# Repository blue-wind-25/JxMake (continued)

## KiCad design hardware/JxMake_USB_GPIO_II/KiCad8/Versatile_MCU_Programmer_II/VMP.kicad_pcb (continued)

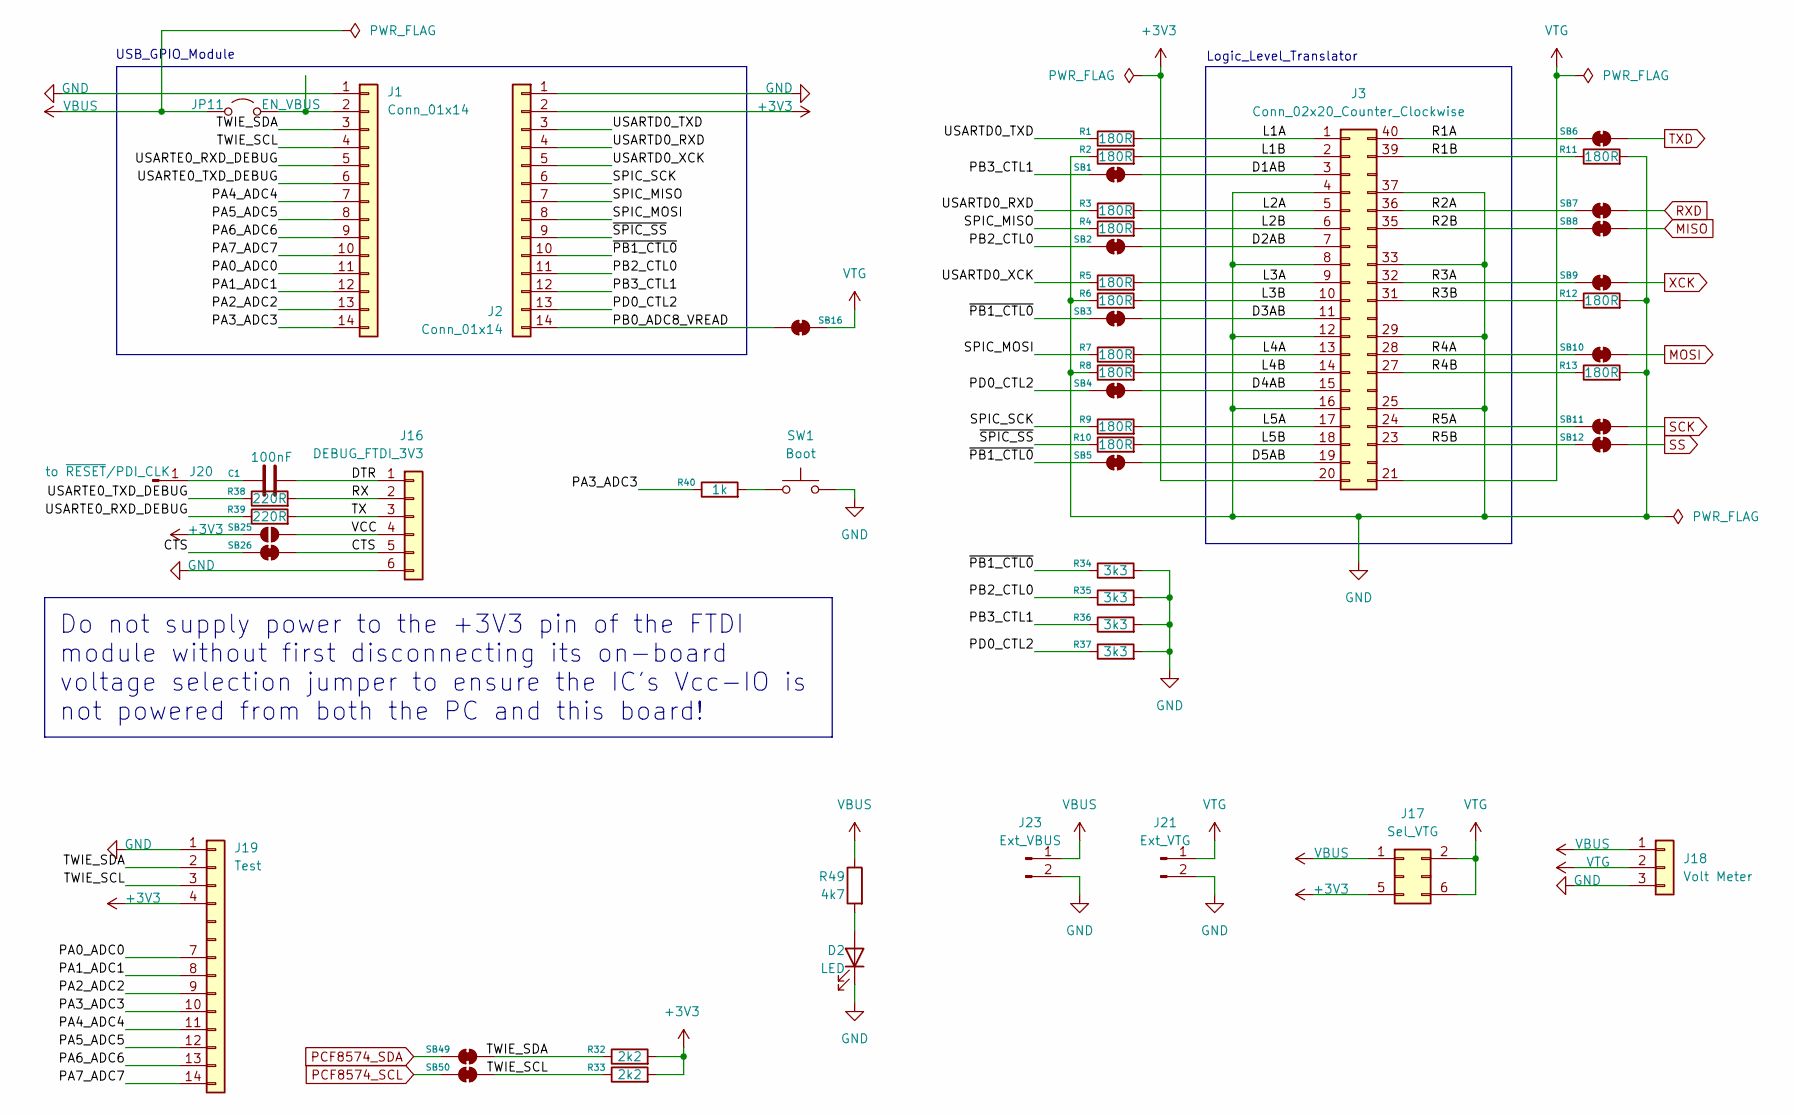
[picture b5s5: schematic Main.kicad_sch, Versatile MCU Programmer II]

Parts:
C1: 100nF; C_0805_2012Metric_Pad1.18x1.45mm_HandSolder
D2: LED; LED_0805_2012Metric_Pad1.15x1.40mm_HandSolder
J1, J2: Conn_01x14; PinHeader_1x14_P2.54mm_Vertical
J3: Conn_02x20_Counter_Clockwise; DIP-40_W25.4mm_LongPads
J16: DEBUG_FTDI_3V3; PinSocket_1x06_P2.54mm_Horizontal
J17: Sel_VTG; PinHeader_2x03_P2.54mm_Vertical
J18: Volt Meter; Molex_KK-254_AE-6410-03A_1x03_P2.54mm_Vertical
J19: Test; PinHeader_1x14_P2.54mm_Vertical
J20: to ~{RESET}/PDI_CLK; PinHeader_1x01_P2.54mm_Vertical
J21: Ext_VTG; Molex_KK-254_AE-6410-02A_1x02_P2.54mm_Vertical
J23: Ext_VBUS; Molex_KK-254_AE-6410-02A_1x02_P2.54mm_Vertical
JP11: EN_VBUS; PinHeader_1x02_P2.54mm_Vertical
R1, R2, R3, R4, R5, R6, R7, R8, R9, R10, R11, R12, R13: 180R; R_0805_2012Metric_Pad1.20x1.40mm_HandSolder
R32, R33: 2k2; R_0805_2012Metric_Pad1.20x1.40mm_HandSolder
R34, R35, R36, R37: 3k3; R_0805_2012Metric_Pad1.20x1.40mm_HandSolder
R38, R39: 220R; R_0805_2012Metric_Pad1.20x1.40mm_HandSolder
R40: 1k; R_0805_2012Metric_Pad1.20x1.40mm_HandSolder
R49: 4k7; R_0805_2012Metric_Pad1.20x1.40mm_HandSolder
SB1, SB2, SB3, SB4, SB5, SB6, SB7, SB8, SB9, SB10, SB11, SB12, SB16, SB26, SB49, SB50: Jumper_2_Small_Bridged; SolderJumper-2_P1.3mm_Bridged_Pad1.0x1.5mm
SB25: Jumper_2_Small_Open; SolderJumper-2_P1.3mm_Open_Pad1.0x1.5mm
SW1: Boot; SW_SPST_FSMSM

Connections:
+3V3: J2.2, J3.20, J17.5, J19.4, R32.2, R33.2, SB25.1 (A); also elsewhere on the board
/Main/CTS: J16.5, SB26.1 (A), SB26.2 (B)
/Main/D1AB: J3.3, SB1.2 (B)
/Main/D2AB: J3.7, SB2.2 (B)
/Main/D3AB: J3.11, SB3.2 (B)
/Main/D4AB: J3.15, SB4.2 (B)
/Main/D5AB: J3.19, SB5.2 (B)
/Main/DTR: C1.2, J16.1
/Main/L1A: J3.1, R1.2
/Main/L1B: J3.2, R2.2
/Main/L2A: J3.5, R3.2
/Main/L2B: J3.6, R4.2
/Main/L3A: J3.9, R5.2
/Main/L3B: J3.10, R6.2
/Main/L4A: J3.13, R7.2
/Main/L4B: J3.14, R8.2
/Main/L5A: J3.17, R9.2
/Main/L5B: J3.18, R10.2
/Main/PA0_ADC0: J1.11, J19.7
/Main/PA1_ADC1: J1.12, J19.8
/Main/PA2_ADC2: J1.13, J19.9
/Main/PA3_ADC3: J1.14, J19.10, R40.1
/Main/PA4_ADC4: J1.7, J19.11
/Main/PA5_ADC5: J1.8, J19.12
/Main/PA6_ADC6: J1.9, J19.13
/Main/PA7_ADC7: J1.10, J19.14
/Main/PB0_ADC8_VREAD: J2.14, SB16.2 (B)
/Main/PB2_CTL0: J2.11, R35.1, SB2.1 (A)
/Main/PB3_CTL1: J2.12, R36.1, SB1.1 (A)
/Main/PD0_CTL2: J2.13, R37.1, SB4.1 (A)
/Main/R1A: J3.40, SB6.1 (A)
/Main/R1B: J3.39, R11.1
/Main/R2A: J3.36, SB7.1 (A)
/Main/R2B: J3.35, SB8.1 (A)
/Main/R3A: J3.32, SB9.1 (A)
/Main/R3B: J3.31, R12.1
/Main/R4A: J3.28, SB10.1 (A)
/Main/R4B: J3.27, R13.1
/Main/R5A: J3.24, SB11.1 (A)
/Main/R5B: J3.23, SB12.1 (A)
/Main/RX: J16.2, R38.2
/Main/SPIC_MISO: J2.7, R4.1
/Main/SPIC_MOSI: J2.8, R7.1
/Main/SPIC_SCK: J2.6, R9.1
/Main/TWIE_SCL: J1.4, J19.3, R33.1, SB50.2 (B)
/Main/TWIE_SDA: J1.3, J19.2, R32.1, SB49.2 (B)
/Main/TX: J16.3, R39.2
/Main/USARTD0_RXD: J2.4, R3.1
/Main/USARTD0_TXD: J2.3, R1.1
/Main/USARTD0_XCK: J2.5, R5.1
/Main/USARTE0_RXD_DEBUG: J1.5, R39.1
/Main/USARTE0_TXD_DEBUG: J1.6, R38.1
/Main/VCC: J16.4, SB25.2 (B)
/Main/~PB1_CTL0: J2.10, R34.1, SB3.1 (A), SB5.1 (A)
/Main/~SPIC_SS: J2.9, R10.1
GND: D2.1 (K), J1.1, J2.1, J3.4, J3.8, J3.12, J3.16, J3.25, J3.29, J3.33, J3.37, J16.6, J18.3, J19.1, J21.2, J23.2, R2.1, R6.1, R8.1, R11.2, R12.2, R13.2, R34.2, R35.2, R36.2, R37.2, SW1.2; also elsewhere on the board
MISO: SB8.2 (B); also elsewhere on the board
MOSI: SB10.2 (B); also elsewhere on the board
unnamed: D2.2 (A), R49.2
unnamed: J1.2, JP11.2 (B)
unnamed: C1.1, J20.1
unnamed: R40.2, SW1.1
PCF8574_SCL: SB50.1 (A); also elsewhere on the board
PCF8574_SDA: SB49.1 (A); also elsewhere on the board
RXD: SB7.2 (B); also elsewhere on the board
SCK: SB11.2 (B); also elsewhere on the board
SS: SB12.2 (B); also elsewhere on the board
TXD: SB6.2 (B); also elsewhere on the board
VBUS: J17.1, J18.1, J23.1, JP11.1 (A), R49.1; also elsewhere on the board
VTG: J3.21, J17.2, J17.6, J18.2, J21.1, SB16.1 (A); also elsewhere on the board
XCK: SB9.2 (B); also elsewhere on the board

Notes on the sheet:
Do not supply power to the +3V3 pin of the FTDI module without first disconnecting its on-board voltage selection jumper to ensure the IC's Vcc-IO is not powered from both the PC and this board!
Logic_Level_Translator
USB_GPIO_Module

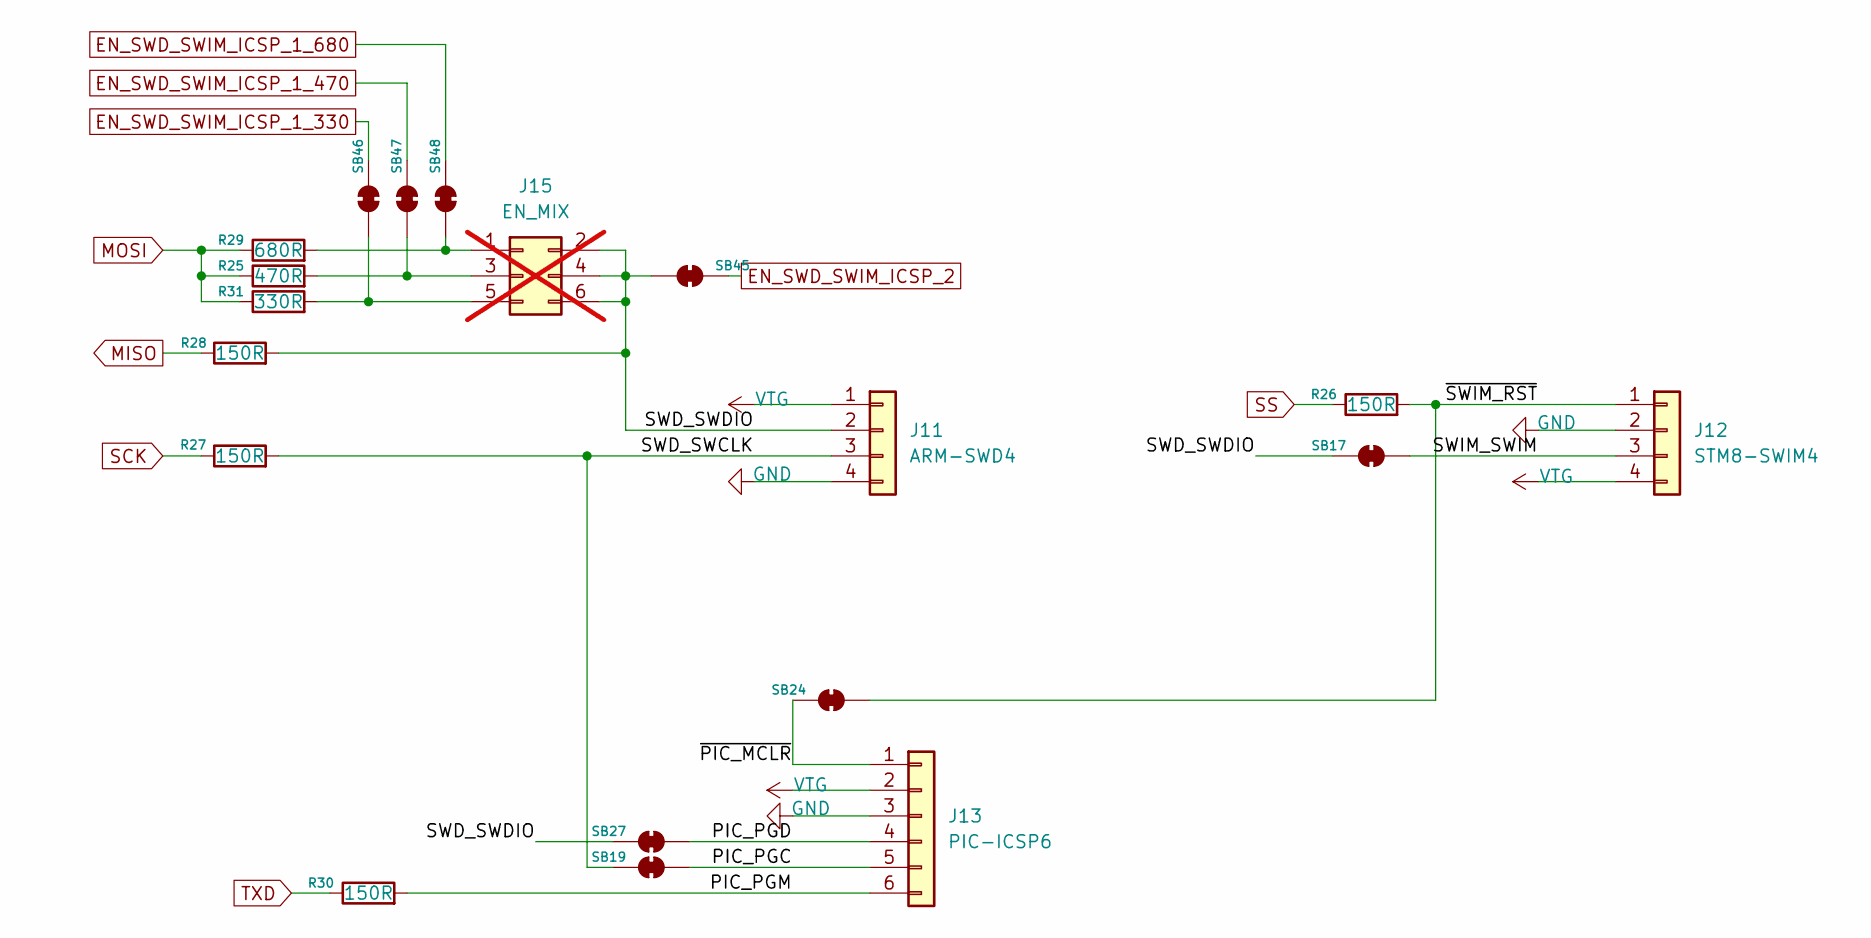
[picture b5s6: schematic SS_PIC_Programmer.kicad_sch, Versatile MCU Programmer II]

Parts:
J11: ARM-SWD4; PinSocket_1x04_P2.54mm_Horizontal
J12: STM8-SWIM4; PinSocket_1x04_P2.54mm_Horizontal
J13: PIC-ICSP6; PinSocket_1x06_P2.54mm_Horizontal
J15: EN_MIX; PinHeader_2x03_P2.54mm_Vertical; not fitted
R25: 470R; R_0805_2012Metric_Pad1.20x1.40mm_HandSolder
R26, R27, R28, R30: 150R; R_1206_3216Metric_Pad1.30x1.75mm_HandSolder
R29: 680R; R_0805_2012Metric_Pad1.20x1.40mm_HandSolder
R31: 330R; R_1206_3216Metric_Pad1.30x1.75mm_HandSolder
SB17, SB19, SB24, SB27, SB45, SB46, SB47, SB48: Jumper_2_Small_Bridged; SolderJumper-2_P1.3mm_Bridged_Pad1.0x1.5mm

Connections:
/SWD_SWIM_PIC_Programmer/PIC_PGC: J13.5, SB19.2 (B)
/SWD_SWIM_PIC_Programmer/PIC_PGD: J13.4, SB27.2 (B)
/SWD_SWIM_PIC_Programmer/PIC_PGM: J13.6, R30.2
/SWD_SWIM_PIC_Programmer/SWD_SWCLK: J11.3, R27.2, SB19.1 (A)
/SWD_SWIM_PIC_Programmer/SWD_SWDIO: J11.2, J15.2, J15.4, J15.6, R28.2, SB17.1 (A), SB27.1 (A), SB45.2 (B)
/SWD_SWIM_PIC_Programmer/SWIM_SWIM: J12.3, SB17.2 (B)
/SWD_SWIM_PIC_Programmer/~PIC_MCLR: J13.1, SB24.1 (A)
/SWD_SWIM_PIC_Programmer/~SWIM_RST: J12.1, R26.2, SB24.2 (B)
EN_SWD_SWIM_ICSP_1_330: SB46.1 (A); also elsewhere on the board
EN_SWD_SWIM_ICSP_1_470: SB47.1 (A); also elsewhere on the board
EN_SWD_SWIM_ICSP_1_680: SB48.1 (A); also elsewhere on the board
EN_SWD_SWIM_ICSP_2: SB45.1 (A); also elsewhere on the board
GND: J11.4, J12.2, J13.3; also elsewhere on the board
MISO: R28.1; also elsewhere on the board
MOSI: R25.1, R29.1, R31.1; also elsewhere on the board
unnamed: J15.1, R29.2, SB48.2 (B)
unnamed: J15.3, R25.2, SB47.2 (B)
unnamed: J15.5, R31.2, SB46.2 (B)
SCK: R27.1; also elsewhere on the board
SS: R26.1; also elsewhere on the board
TXD: R30.1; also elsewhere on the board
VTG: J11.1, J12.4, J13.2; also elsewhere on the board

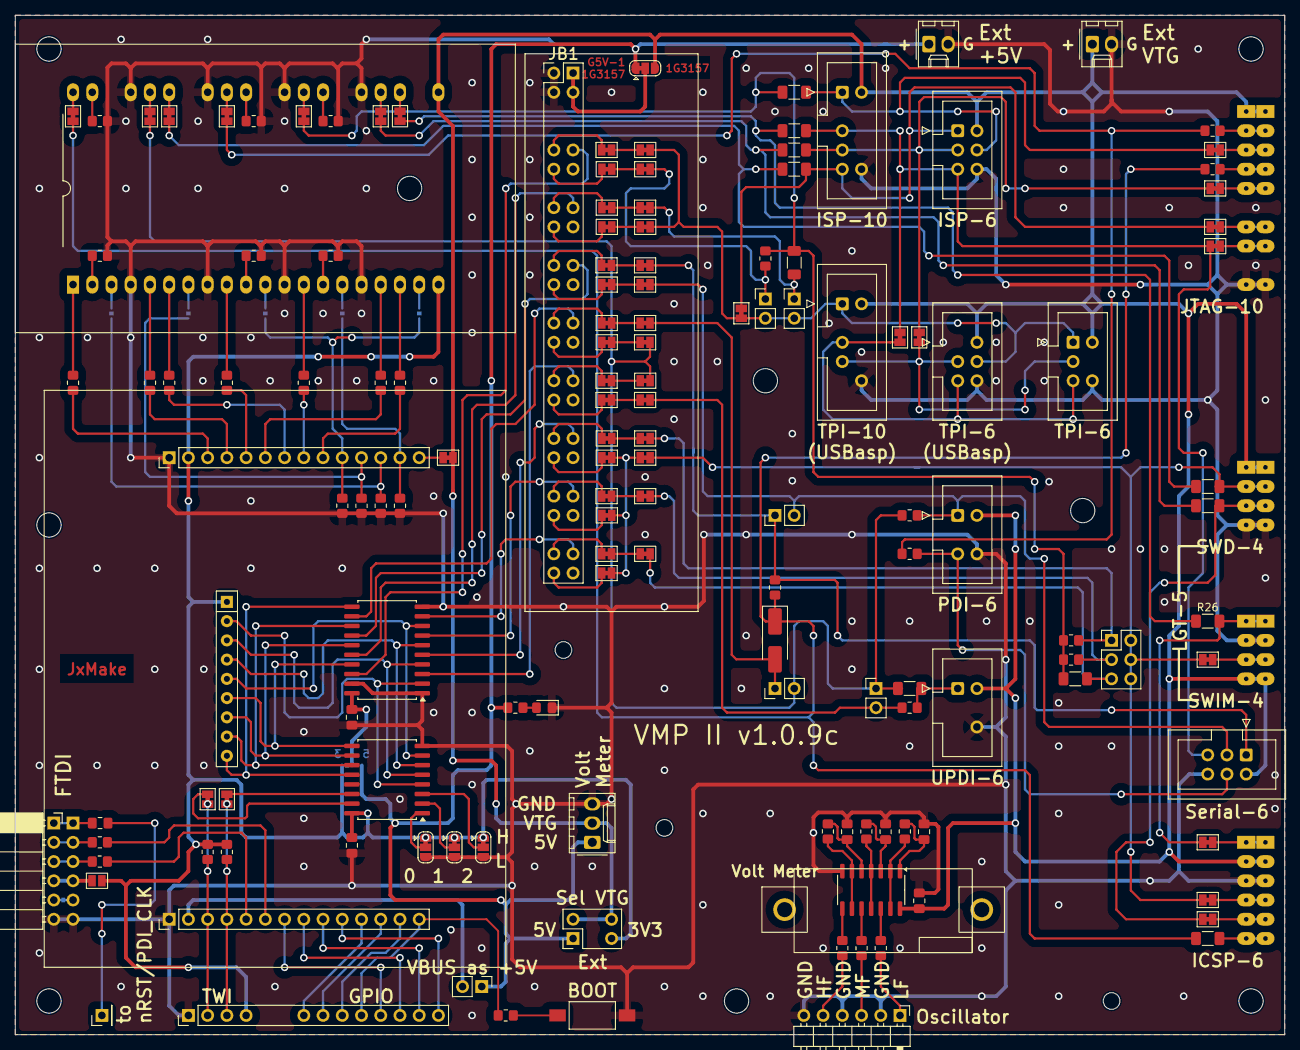
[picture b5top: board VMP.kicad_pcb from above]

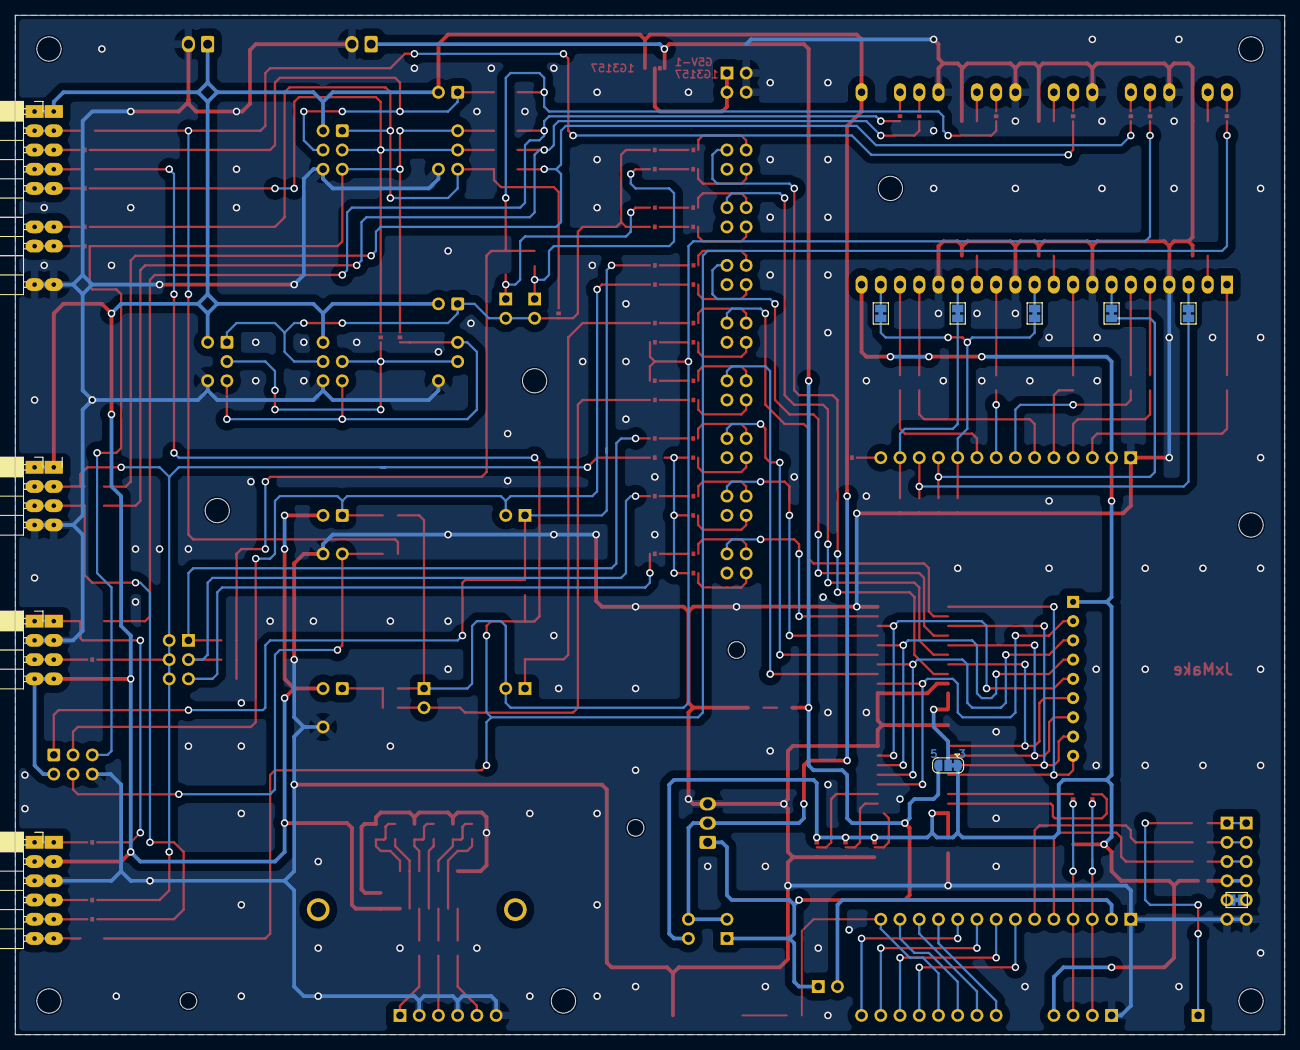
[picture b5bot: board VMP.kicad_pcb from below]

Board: 2 copper layers, 167.6 x 134.6 mm, 169 parts (11 on the bottom side), 166 nets.

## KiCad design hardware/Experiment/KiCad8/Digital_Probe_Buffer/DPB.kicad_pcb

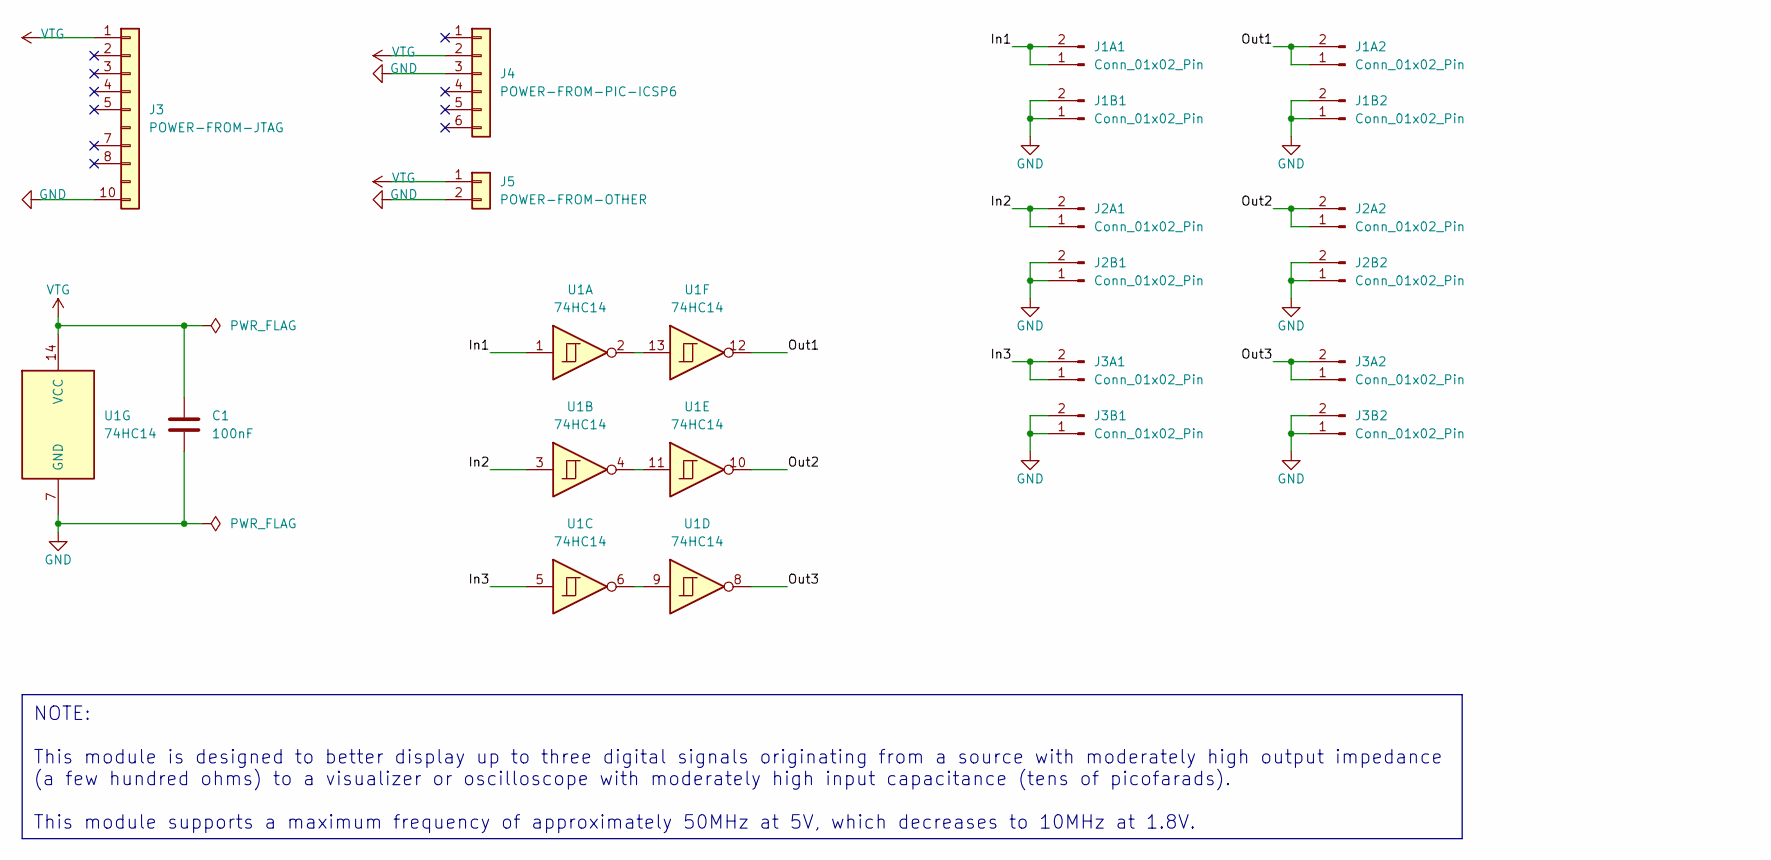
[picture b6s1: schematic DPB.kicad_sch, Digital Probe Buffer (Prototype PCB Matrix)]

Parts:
C1: 100nF; C_Disc_D4.7mm_W2.5mm_P5.00mm
J1A1, J1A2, J1B1, J1B2, J2A1, J2A2, J2B1, J2B2, J3A1, J3A2, J3B1, J3B2: Conn_01x02_Pin; PinHeader_1x02_P2.54mm_Vertical
J3: POWER-FROM-JTAG; PinHeader_1x10_P2.54mm_Horizontal
J4: POWER-FROM-PIC-ICSP6; PinHeader_1x06_P2.54mm_Horizontal
J5: POWER-FROM-OTHER; PinHeader_1x02_P2.54mm_Vertical
U1: 74HC14; DIP-14_W7.62mm

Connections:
/In1: J1A1.1, J1A1.2, U1.1
/In2: J2A1.1, J2A1.2, U1.3
/In3: J3A1.1, J3A1.2, U1.5
/Out1: J1A2.1, J1A2.2, U1.12
/Out2: J2A2.1, J2A2.2, U1.10
/Out3: J3A2.1, J3A2.2, U1.8
GND: C1.2, J1B1.1, J1B1.2, J1B2.1, J1B2.2, J2B1.1, J2B1.2, J2B2.1, J2B2.2, J3.10, J3B1.1, J3B1.2, J3B2.1, J3B2.2, J4.3, J5.2, U1.7 (GND)
unnamed: U1.6, U1.9
unnamed: U1.4, U1.11
unnamed: U1.2, U1.13
VTG: C1.1, J3.1, J4.2, J5.1, U1.14 (VCC)

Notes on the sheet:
NOTE: This module is designed to better display up to three digital signals originating from a source with moderately high output impedance (a few hundred ohms) to a visualizer or oscilloscope with moderately high input capacitance (tens of picofarads). This module supports a maximum frequency of a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

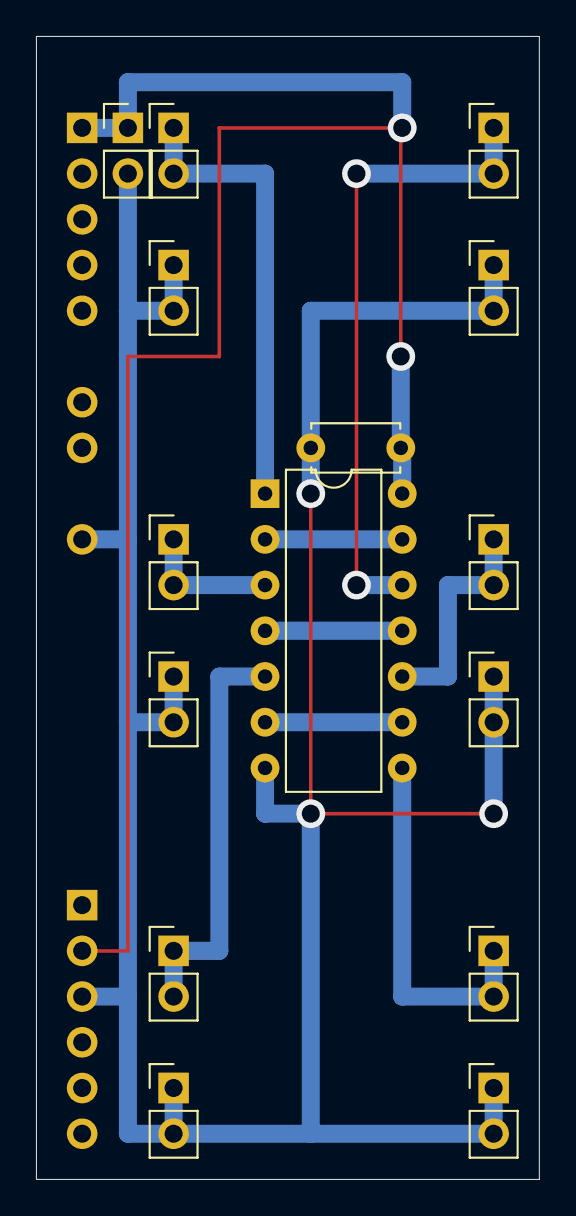
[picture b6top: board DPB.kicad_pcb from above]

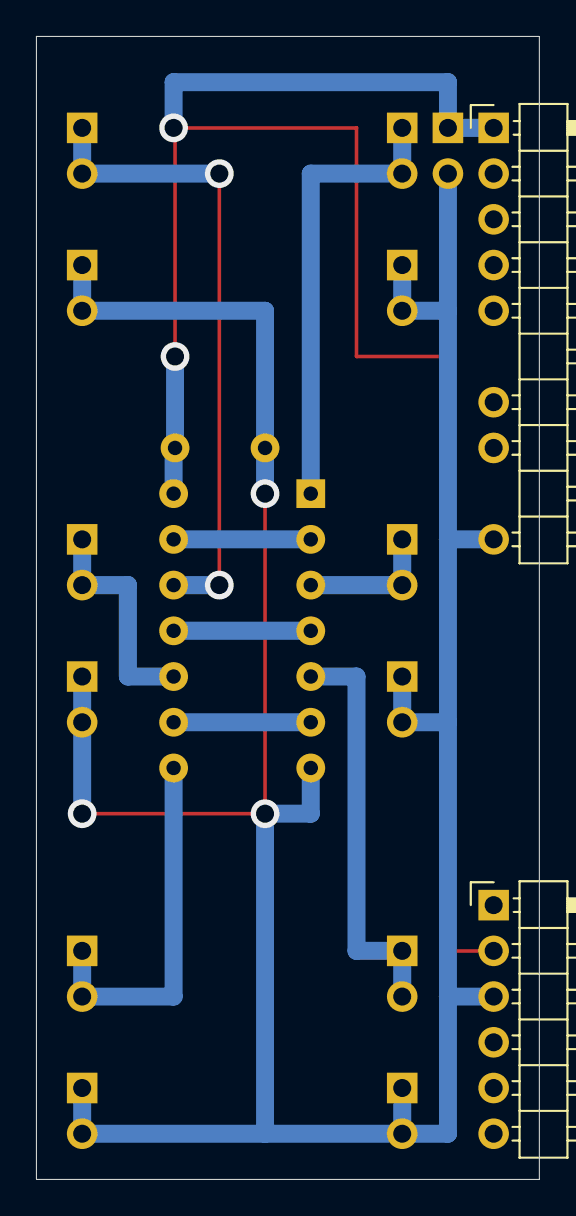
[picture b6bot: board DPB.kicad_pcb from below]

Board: 2 copper layers, 27.9 x 63.5 mm, 17 parts (2 on the bottom side), 11 nets.

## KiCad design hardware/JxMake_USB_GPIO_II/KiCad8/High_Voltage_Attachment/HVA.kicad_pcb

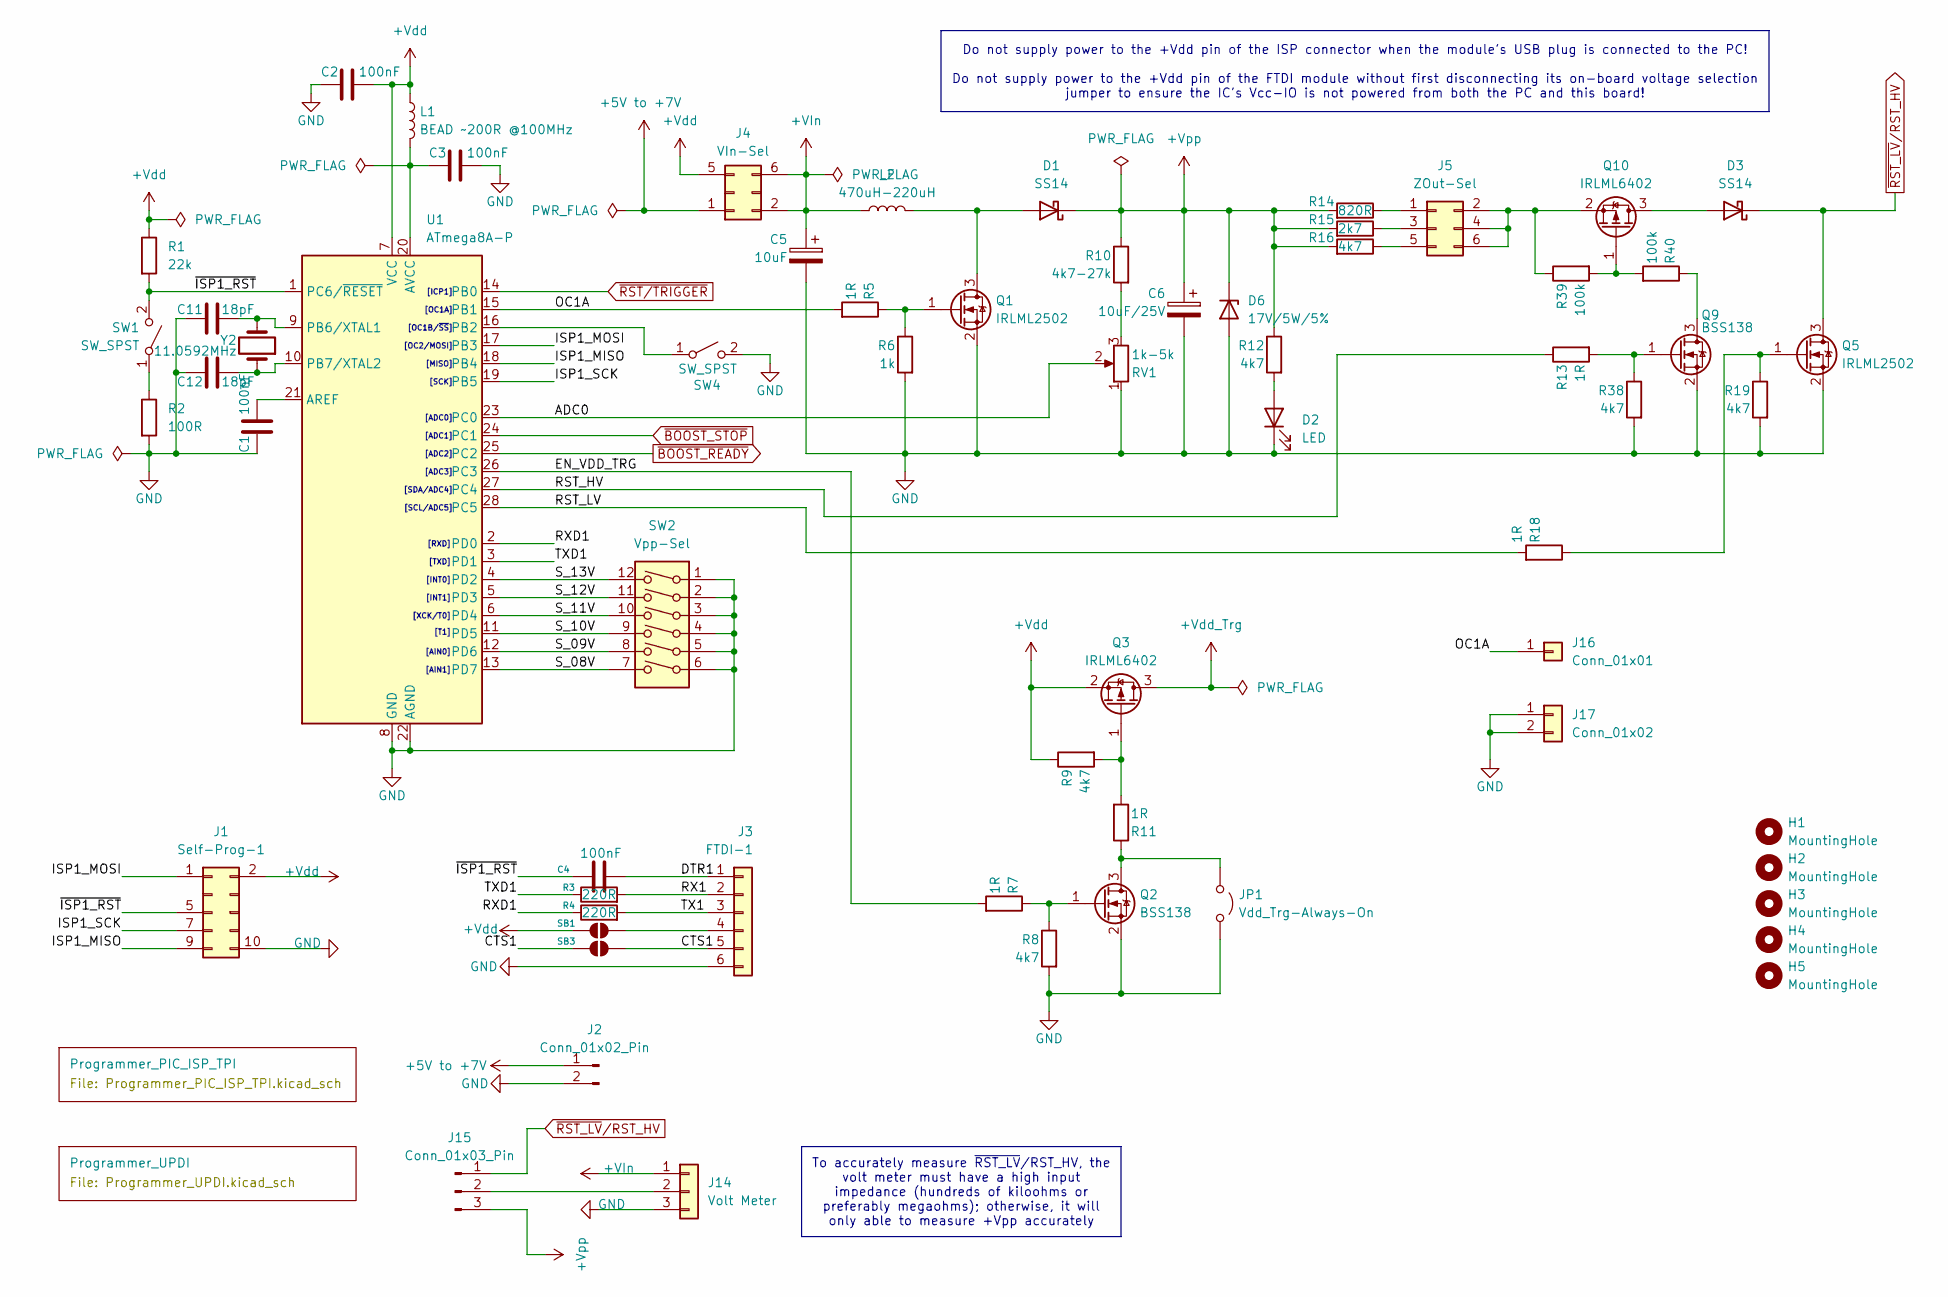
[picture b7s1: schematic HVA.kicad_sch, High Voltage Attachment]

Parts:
C1, C2, C3, C4: 100nF; C_0805_2012Metric_Pad1.18x1.45mm_HandSolder
C5: 10uF; CP_EIA-3528-21_Kemet-B_Pad1.50x2.35mm_HandSolder
C6: 10uF/25V; CP_EIA-3528-21_Kemet-B_Pad1.50x2.35mm_HandSolder
C11, C12: 18pF; C_0805_2012Metric_Pad1.18x1.45mm_HandSolder
D1, D3: SS14; D_SMA
D2: LED; LED_0805_2012Metric_Pad1.15x1.40mm_HandSolder
D6: 17V/5W/5%; D_5W_P10.16mm_Horizontal
H1, H2, H3, H4, H5: MountingHole; MountingHole_3.2mm_M3
J1: Self-Prog-1; IDC-Header_2x05_P2.54mm_Vertical
J2: Conn_01x02_Pin; Molex_KK-254_AE-6410-02A_1x02_P2.54mm_Vertical
J3: FTDI-1; PinSocket_1x06_P2.54mm_Horizontal
J4: VIn-Sel; PinHeader_2x03_P2.54mm_Vertical
J5: ZOut-Sel; PinHeader_2x03_P2.54mm_Vertical
J14: Volt Meter; FanPinHeader_1x03_P2.54mm_Vertical
J15: Conn_01x03_Pin; PinHeader_1x03_P2.54mm_Vertical
J16: Conn_01x01; PinHeader_1x01_P2.54mm_Vertical
J17: Conn_01x02; PinHeader_1x02_P2.54mm_Vertical
JP1: Vdd_Trg-Always-On; PinHeader_2x01_P2.54mm_Vertical
L1: BEAD ~200R @100MHz; L_0805_2012Metric_Pad1.15x1.40mm_HandSolder
L2: 470uH-220uH; L_Radial_D10.0mm_P5.00mm_Fastron_07M
Q1, Q5: IRLML2502; SOT-23_Handsoldering
Q2, Q9: BSS138; SOT-23_Handsoldering
Q3, Q10: IRLML6402; SOT-23_Handsoldering
R1: 22k; R_0805_2012Metric_Pad1.20x1.40mm_HandSolder
R2: 100R; R_0805_2012Metric_Pad1.20x1.40mm_HandSolder
R3, R4: 220R; R_0805_2012Metric_Pad1.20x1.40mm_HandSolder
R5, R7, R11, R13, R18: 1R; R_0805_2012Metric_Pad1.20x1.40mm_HandSolder
R6: 1k; R_0805_2012Metric_Pad1.20x1.40mm_HandSolder
R8, R9, R12, R16, R19, R38: 4k7; R_0805_2012Metric_Pad1.20x1.40mm_HandSolder
R10: 4k7-27k; R_0805_2012Metric_Pad1.20x1.40mm_HandSolder
R14: 820R; R_0805_2012Metric_Pad1.20x1.40mm_HandSolder
R15: 2k7; R_0805_2012Metric_Pad1.20x1.40mm_HandSolder
R39, R40: 100k; R_0805_2012Metric_Pad1.20x1.40mm_HandSolder
RV1: 1k-5k; Potentiometer_Bourns_3296W_Vertical
SB1, SB3: Jumper_2_Small_Bridged; SolderJumper-2_P1.3mm_Open_RoundedPad1.0x1.5mm
SW1, SW4: SW_SPST; SW_SPST_FSMSM
SW2: Vpp-Sel; SW_DIP_SPSTx06_Slide_9.78x17.42mm_W7.62mm_P2.54mm
U1: ATmega8A-P; DIP-28_W7.62mm
Y2: 11.0592MHz; Crystal_SMD_HC49-SD

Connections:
+5V to +7V: J2.1, J4.1
+VIn: C5.1, J4.2, J4.6, J14.1, L2.1
+Vdd: C2.2, J1.2, J4.5, L1.1, Q3.2 (S), R1.1, R9.1, SB1.1 (A), U1.7 (VCC); also elsewhere on the board
+Vdd_Trg: Q3.3 (D); also elsewhere on the board
+Vpp: C6.1, D1.1 (K), D6.1 (K), J15.3, R10.1, R12.1, R14.2, R15.2, R16.2; also elsewhere on the board
/ADC0: RV1.2, U1.23 (PC0)
/CTS1: J3.5, SB3.1 (A), SB3.2 (B)
/DTR1: C4.2, J3.1
/EN_VDD_TRG: R7.2, U1.26 (PC3)
/ISP1_MISO: J1.9, U1.18 (PB4)
/ISP1_MOSI: J1.1, U1.17 (PB3)
/ISP1_SCK: J1.7, U1.19 (PB5)
/OC1A: J16.1, R5.2, U1.15 (PB1)
/RST_HV: R13.1, U1.27 (PC4)
/RST_LV: R18.2, U1.28 (PC5)
/RX1: J3.2, R3.2
/RXD1: R4.1, U1.2 (PD0)
/S_08V: SW2.7, U1.13 (PD7)
/S_09V: SW2.8, U1.12 (PD6)
/S_10V: SW2.9, U1.11 (PD5)
/S_11V: SW2.10, U1.6 (PD4)
/S_12V: SW2.11, U1.5 (PD3)
/S_13V: SW2.12, U1.4 (PD2)
/TX1: J3.3, R4.2
/TXD1: R3.1, U1.3 (PD1)
/~ISP1_RST: C4.1, J1.5, R1.2, SW1.2 (B), U1.1 (PC6/~RESET)
GND: C1.1, C2.1, C3.2, C5.2, C6.2, C11.1, C12.1, D2.1 (K), D6.2 (A), J1.10, J2.2, J3.6, J14.3, J17.1, J17.2, JP1.2 (B), Q1.2 (S), Q2.2 (S), Q5.2 (S), Q9.2 (S), R2.2, R6.2, R8.2, R19.2, R38.2, RV1.1, SW2.1, SW2.2, SW2.3, SW2.4, SW2.5, SW2.6, SW4.2 (B), U1.8 (GND), U1.22 (AGND); also elsewhere on the board
unnamed: D1.2 (A), L2.2, Q1.3 (D)
unnamed: D2.2 (A), R12.2
unnamed: D3.2 (A), Q10.3 (D)
unnamed: J3.4, SB1.2 (B)
unnamed: J5.1, R14.1
unnamed: J5.2, J5.4, J5.6, Q10.2 (S), R39.1
unnamed: J5.3, R15.1
unnamed: J5.5, R16.1
unnamed: J14.2, J15.2
unnamed: JP1.1 (A), Q2.3 (D), R11.1
unnamed: Q1.1 (G), R5.1, R6.1
unnamed: Q2.1 (G), R7.1, R8.1
unnamed: Q3.1 (G), R9.2, R11.2
unnamed: Q5.1 (G), R18.1, R19.1
unnamed: Q9.3 (D), R40.1
unnamed: Q9.1 (G), R13.2, R38.1
unnamed: Q10.1 (G), R39.2, R40.2
unnamed: R10.2, RV1.3
unnamed: R2.1, SW1.1 (A)
unnamed: SW4.1 (A), U1.16 (PB2)
unnamed: C1.2, U1.21 (AREF)
unnamed: C3.1, L1.2, U1.20 (AVCC)
unnamed: C11.2, U1.9 (PB6/XTAL1), Y2.2
unnamed: C12.2, U1.10 (PB7/XTAL2), Y2.1
~BOOST_READY: U1.25 (PC2); also elsewhere on the board
~BOOST_STOP: U1.24 (PC1); also elsewhere on the board
~RST_LV/RST_HV: D3.1 (K), J15.1, Q5.3 (D); also elsewhere on the board
~RST/TRIGGER: U1.14 (PB0); also elsewhere on the board

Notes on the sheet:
Do not supply power to the +Vdd pin of the ISP connector when the module's USB plug is connected to the PC! Do not supply power to the +Vdd pin of the FTDI module without first disconnecting its on-board voltage selection jumper to ensure the IC's Vcc-IO is not powered from both the PC and this boa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
To accurately measure ~{RST_LV}/RST_HV, the volt meter must have a high input impedance (hundreds of kiloohms or preferably megaohms); otherwise, it will only able to measure +Vpp accurately
[ADC3]
[TXD]
[ADC2]
[OC1A]
[INT0]
[ICP1]
[INT1]
[ADC1]
[ADC0]
[XCK/T0]
[T1]
[RXD]
[SDA/ADC4]
[SCL/ADC5]
[MISO]
[SCK]
[OC2/MOSI]
[OC1B/~{SS}]
[AIN0]
[AIN1]
